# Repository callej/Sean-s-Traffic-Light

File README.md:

# Sean-s-Traffic-Light

A small demo project to give an overview of how KiCad works.

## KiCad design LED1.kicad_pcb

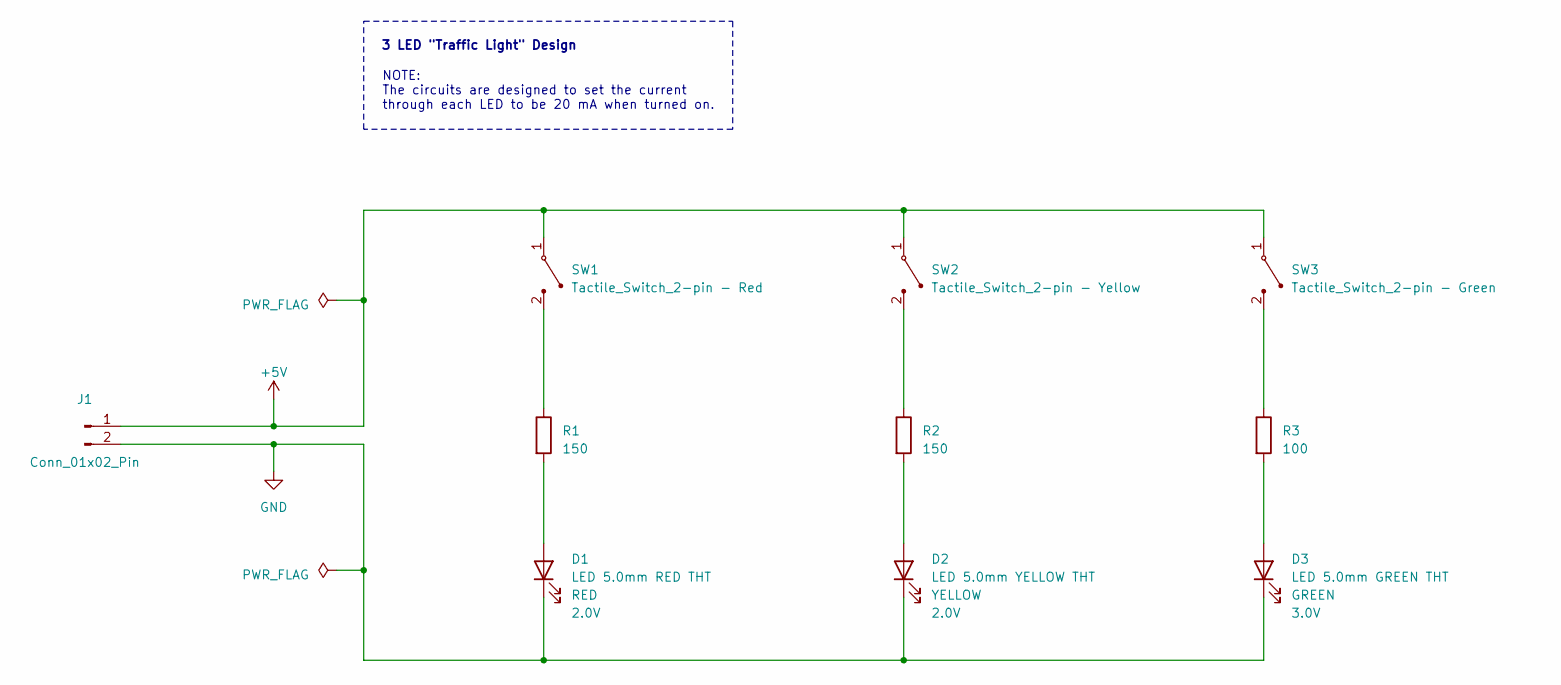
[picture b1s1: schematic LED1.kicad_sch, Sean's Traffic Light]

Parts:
D1: LED 5.0mm RED THT; LED_D5.0mm RED THT; Voltage 2.0V
D2: LED 5.0mm YELLOW THT; LED_D5.0mm YELLOW THT; Voltage 2.0V
D3: LED 5.0mm GREEN THT; LED_D5.0mm GREEN THT; Voltage 3.0V
J1: Conn_01x02_Pin; PinHeader_1x02_P2.54mm_Vertical
R1, R2: 150; R_Axial_DIN0204_L3.6mm_D1.6mm_P7.62mm_Horizontal
R3: 100; R_Axial_DIN0204_L3.6mm_D1.6mm_P7.62mm_Horizontal
SW1: Tactile_Switch_2-pin - Red; Tactile Switch - 6 x 6 mm - 2-pin - Red
SW2: Tactile_Switch_2-pin - Yellow; Tactile Switch - 6 x 6 mm - 2-pin - Yellow
SW3: Tactile_Switch_2-pin - Green; Tactile Switch - 6 x 6 mm - 2-pin - Green

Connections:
+5V: J1.1, SW1.1, SW2.1, SW3.1
GND: D1.1 (K), D2.1 (K), D3.1 (K), J1.2
unnamed: D1.2 (A), R1.2
unnamed: D2.2 (A), R2.2
unnamed: D3.2 (A), R3.2
unnamed: R1.1, SW1.2
unnamed: R2.1, SW2.2
unnamed: R3.1, SW3.2

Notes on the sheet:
NOTE: The circuits are designed to set the current through each LED to be 20 mA when turned on.
3 LED "Traffic Light" Design

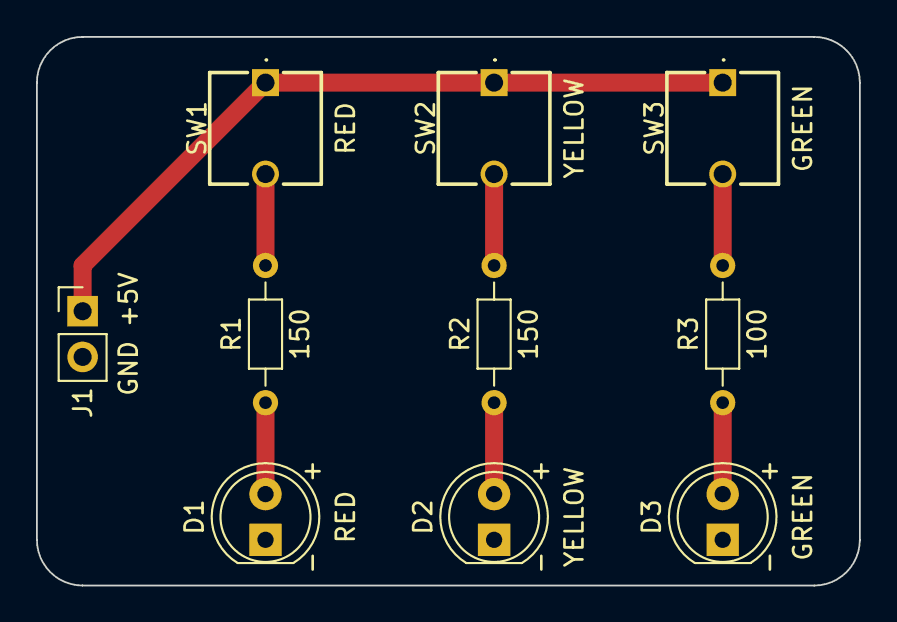
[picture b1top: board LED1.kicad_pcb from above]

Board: 2 copper layers, 45.7 x 30.5 mm, 10 parts (0 on the bottom side), 8 nets.

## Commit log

2023-05-02 First commit of the Sean's Traffic Light Project
2023-05-02 Create LICENSE
2023-05-13 Improved the layout by rotating the tactile switches.
